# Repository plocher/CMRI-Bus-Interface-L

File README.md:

# CMRI-Bus-Interface-L
## License: Creative Commons Attribution-NonCommercial-ShareAlike

RS422/485 driver for CMRI-Net - large 3" Tyco rail size

Adapter board for interfacing with CMRI Bus traffic using MRCS ‘duino example code. Uses an optional onboard 555 to generate TX/RX enable based on processor I/O direction

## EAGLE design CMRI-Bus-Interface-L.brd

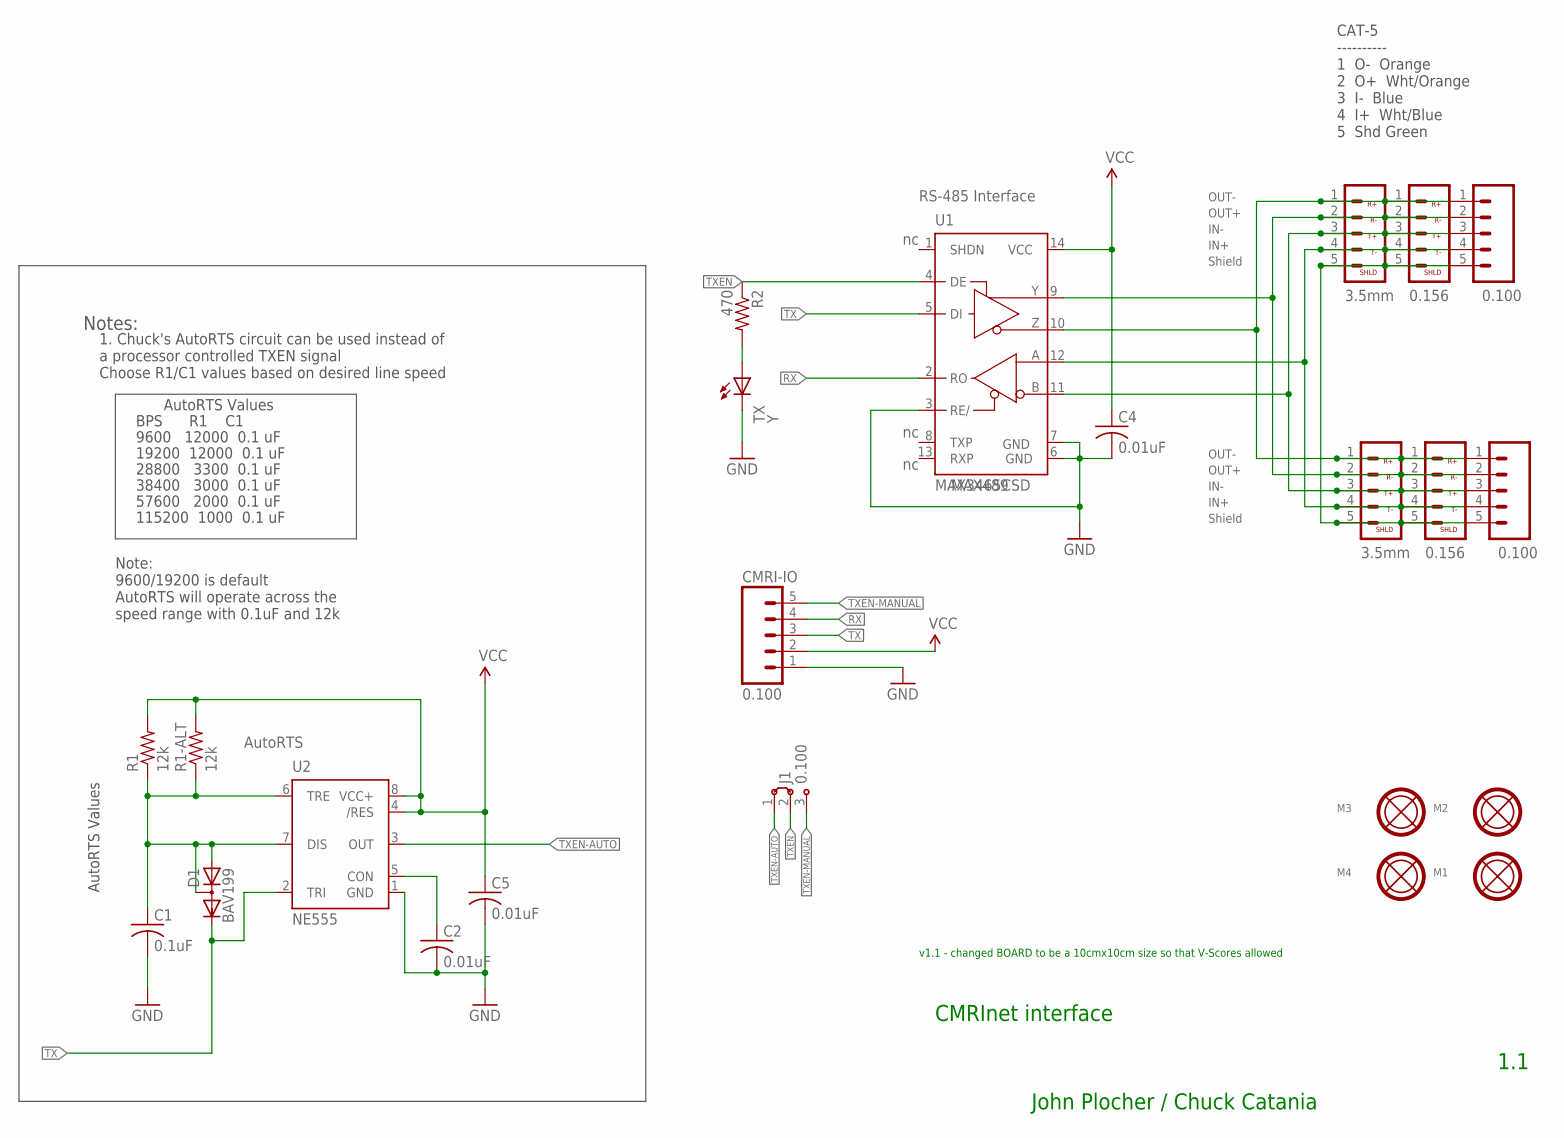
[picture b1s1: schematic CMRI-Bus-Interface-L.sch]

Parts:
C1: 0.1uF; 0603-CAP
C2, C4, C5: 0.01uF; 0603-CAP
CMRI-IO: 0.100; 1X05-CMRI-IO
CMRINET1, CMRINET2: 3.5mm; CMRINET-3.5MM
CMRINET3, CMRINET4: 0.156; KK-156-5
CON1, CON2: 0.100; 1X05_LOCK
D1: BAV199; SOT23
J1: 0.100; J3-254
M1, M2, M3, M4: MOUNTINGHOLE
R1: 12k; AXIAL-0.4-RES
R1-ALT: 12k; 0805-RES
R2: 470; 0805-RES
TX: Y; 0603-LED
U1: MAX3465CSD; SO14
U2: NE555; SO08

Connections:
GND: C1.2, C2.2, C4.2, C5.2, CMRI-IO.1, TX.C, U1.3 (RE/), U1.6 (GND), U1.7 (GND), U2.1 (GND)
IN+: CMRINET1.4, CMRINET2.4, CMRINET3.4, CMRINET4.4, CON1.4, CON2.4, U1.12 (A)
IN-: CMRINET1.3, CMRINET2.3, CMRINET3.3, CMRINET4.3, CON1.3, CON2.3, U1.11 (B)
unnamed: R2.2, TX.A
unnamed: C2.1, U2.5 (CON)
unnamed: C1.1, D1.1 (A), D1.3 (AC), R1.P$1 (1), R1-ALT.1, U2.6 (TRE), U2.7 (DIS)
OUT+: CMRINET1.2, CMRINET2.2, CMRINET3.2, CMRINET4.2, CON1.2, CON2.2, U1.9 (Y)
OUT-: CMRINET1.1, CMRINET2.1, CMRINET3.1, CMRINET4.1, CON1.1, CON2.1, U1.10 (Z)
RX: CMRI-IO.4, U1.2 (RO)
SHIELD: CMRINET1.5, CMRINET2.5, CMRINET3.5, CMRINET4.5, CON1.5, CON2.5
TX: CMRI-IO.3, D1.2 (C), U1.5 (DI), U2.2 (TRI)
TXEN: J1.2, R2.1, U1.4 (DE)
TXEN-AUTO: J1.1, U2.3 (OUT)
TXEN-MANUAL: CMRI-IO.5, J1.3
VCC: C4.1, C5.1, CMRI-IO.2, R1.P$2 (2), R1-ALT.2, U1.14 (VCC), U2.4 (/RES), U2.8 (VCC+)

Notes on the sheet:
MAX489
RS-485 Interface
Notes:
IN+
IN-
OUT+
OUT-
1. Chuck's AutoRTS circuit can be used instead of a processor controlled TXEN signal Choose R1/C1 values based on desired line speed
AutoRTS
AutoRTS Values
9600 12000 0.1 uF
19200 12000 0.1 uF
38400 3000 0.1 uF
57600 2000 0.1 uF
115200 1000 0.1 uF
BPS R1 C1
Shield
CAT-5 ---------- 1 O- Orange 2 O+ Wht/Orange 3 I- Blue 4 I+ Wht/Blue 5 Shd Green
28800 3300 0.1 uF
Note: 9600/19200 is default AutoRTS will operate across the speed range with 0.1uF and 12k
1.1
CMRInet interface
John Plocher / Chuck Catania
v1.1 - changed BOARD to be a 10cmx10cm size so that V-Scores allowed

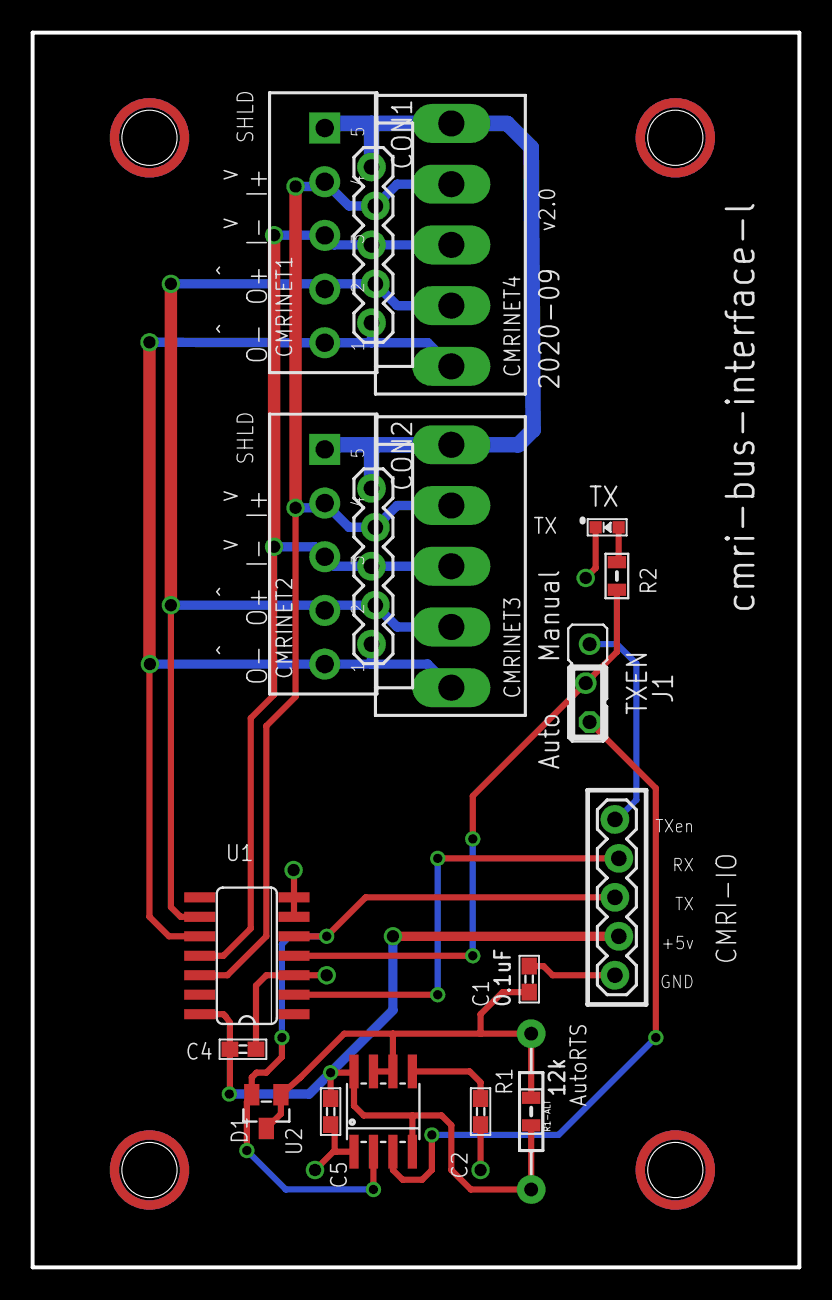
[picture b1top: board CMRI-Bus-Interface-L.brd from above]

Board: 2 copper layers, 50.0 x 80.5 mm, 23 parts (0 on the bottom side), 15 nets.

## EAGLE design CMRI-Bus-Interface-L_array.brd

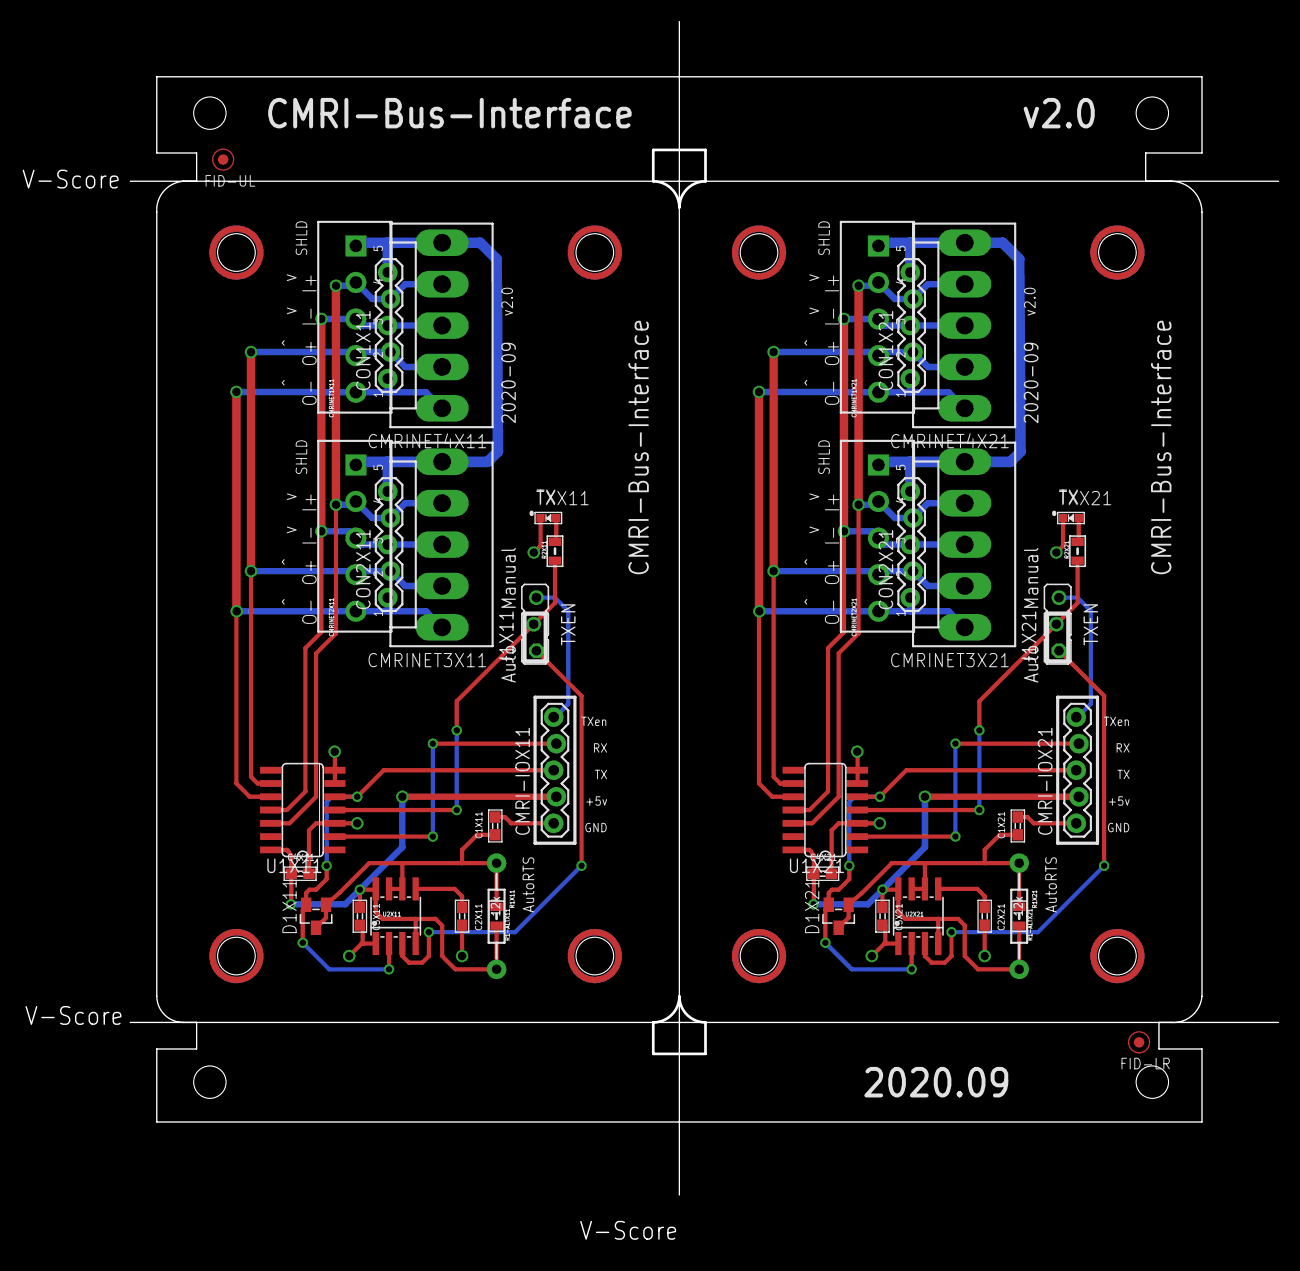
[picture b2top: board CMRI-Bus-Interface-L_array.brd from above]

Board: 2 copper layers, 120.1 x 117.3 mm, 49 parts (0 on the bottom side), 30 nets.

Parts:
C1X11, C1X21: 0.1uF; 0603-CAP
C2X11, C2X21, C4X11, C4X21, C5X11, C5X21: .01uF; 0603-CAP
CMRI-IOX11, CMRI-IOX21: 0.100; 1X05-CMRI-IO
CMRINET1X11, CMRINET1X21, CMRINET2X11, CMRINET2X21: 3.5mm; CMRINET-3.5MM
CMRINET3X11, CMRINET3X21, CMRINET4X11, CMRINET4X21: 0.156; KK-156-5
CON1X11, CON1X21, CON2X11, CON2X21: 0.100; 1X05_LOCK
D1X11, D1X21: BAV199; SOT23
FID-LR: FIDUCIAL; FIDUCIAL_1MM
FID-UL: FIDUCIAL; FIDUCIAL_1MM
J1X11, J1X21: 0.100; J3-254
M1X11, M1X21, M2X11, M2X21, M3X11, M3X21, M4X11, M4X21: MOUNTINGHOLE
R1-ALTX11, R1-ALTX21: 12k; 0805-RES
R1X11, R1X21: 12k; AXIAL-0.4-RES
R2X11, R2X21: 470; 0805-RES
TXX11, TXX21: Y; 0603-LED
U1X11, U1X21: MAX3465CSD; SO14
U2X1: BOARD; BOARD-10X8X2-TEMPLATE
U2X11, U2X21: NE555; SO08

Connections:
GNDX11: C1X11.2, C2X11.2, C4X11.2, C5X11.2, CMRI-IOX11.1, TXX11.C, U1X11.3, U1X11.6, U1X11.7, U2X11.1
GNDX21: C1X21.2, C2X21.2, C4X21.2, C5X21.2, CMRI-IOX21.1, TXX21.C, U1X21.3, U1X21.6, U1X21.7, U2X21.1
IN+X11: CMRINET1X11.4, CMRINET2X11.4, CMRINET3X11.4, CMRINET4X11.4, CON1X11.4, CON2X11.4, U1X11.12
IN+X21: CMRINET1X21.4, CMRINET2X21.4, CMRINET3X21.4, CMRINET4X21.4, CON1X21.4, CON2X21.4, U1X21.12
IN-X11: CMRINET1X11.3, CMRINET2X11.3, CMRINET3X11.3, CMRINET4X11.3, CON1X11.3, CON2X11.3, U1X11.11
IN-X21: CMRINET1X21.3, CMRINET2X21.3, CMRINET3X21.3, CMRINET4X21.3, CON1X21.3, CON2X21.3, U1X21.11
unnamed: R2X11.2, TXX11.A
unnamed: R2X21.2, TXX21.A
unnamed: C2X11.1, U2X11.5
unnamed: C2X21.1, U2X21.5
unnamed: C1X11.1, D1X11.1, D1X11.3, R1-ALTX11.1, R1X11.P$1, U2X11.6, U2X11.7
unnamed: C1X21.1, D1X21.1, D1X21.3, R1-ALTX21.1, R1X21.P$1, U2X21.6, U2X21.7
OUT+X11: CMRINET1X11.2, CMRINET2X11.2, CMRINET3X11.2, CMRINET4X11.2, CON1X11.2, CON2X11.2, U1X11.9
OUT+X21: CMRINET1X21.2, CMRINET2X21.2, CMRINET3X21.2, CMRINET4X21.2, CON1X21.2, CON2X21.2, U1X21.9
OUT-X11: CMRINET1X11.1, CMRINET2X11.1, CMRINET3X11.1, CMRINET4X11.1, CON1X11.1, CON2X11.1, U1X11.10
OUT-X21: CMRINET1X21.1, CMRINET2X21.1, CMRINET3X21.1, CMRINET4X21.1, CON1X21.1, CON2X21.1, U1X21.10
RXX11: CMRI-IOX11.4, U1X11.2
RXX21: CMRI-IOX21.4, U1X21.2
SHIELDX11: CMRINET1X11.5, CMRINET2X11.5, CMRINET3X11.5, CMRINET4X11.5, CON1X11.5, CON2X11.5
SHIELDX21: CMRINET1X21.5, CMRINET2X21.5, CMRINET3X21.5, CMRINET4X21.5, CON1X21.5, CON2X21.5
TXEN-AUTOX11: J1X11.1, U2X11.3
TXEN-AUTOX21: J1X21.1, U2X21.3
TXEN-MANUALX11: CMRI-IOX11.5, J1X11.3
TXEN-MANUALX21: CMRI-IOX21.5, J1X21.3
TXENX11: J1X11.2, R2X11.1, U1X11.4
TXENX21: J1X21.2, R2X21.1, U1X21.4
TXX11: CMRI-IOX11.3, D1X11.2, U1X11.5, U2X11.2
TXX21: CMRI-IOX21.3, D1X21.2, U1X21.5, U2X21.2
VCCX11: C4X11.1, C5X11.1, CMRI-IOX11.2, R1-ALTX11.2, R1X11.P$2, U1X11.14, U2X11.4, U2X11.8
VCCX21: C4X21.1, C5X21.1, CMRI-IOX21.2, R1-ALTX21.2, R1X21.P$2, U1X21.14, U2X21.4, U2X21.8

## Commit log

2020-03-07 Initial version
2020-04-25 v1.1 - changed BOARD to be a 10cmx10cm size so that V-Scores allowed
2020-05-04 updated tags
2020-09-12 added omni-graphic
2020-09-19 added missing component values
2020-09-21 SMT cost reduce
2020-10-05 added values for connectors
2020-10-06 normalized values
